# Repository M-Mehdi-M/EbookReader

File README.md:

## MAHMOUDI Mohammadmehdi 332CB 

# Description
EbookReader is an open-source hardware development platform featuring an E-Paper display, environmental sensing, and low-power connectivity options. Perfect for IoT projects, information displays, and environmental monitoring applications.

## 📋 Overview
This project provides a complete hardware platform built around the ESP32-C6 microcontroller with built-in WiFi 6 and Bluetooth 5 LE connectivity. The E-Paper display offers excellent visibility in various lighting conditions with minimal power consumption.

## 🔌 Hardware Architecture and Components

- **Microcontroller**: ESP32-C6-WROOM-1-N8
  - RISC-V core with WiFi 6 and Bluetooth 5 LE
  - Operating at 3.3V

- **Display**: E-Paper display module
  - SPI interface
  - Ultra-low power consumption when not refreshing

- **Storage**: 
  - microSD card slot (SPI)
  - 64MB External NOR Flash (W25Q512JVEIQ)

- **Sensors**:
  - BME688 Environmental sensor (temperature, humidity, pressure, gas)
  - Battery voltage monitoring

- **Power Management**:
  - Li-Po battery charging circuit
  - Fuel gauge (MAX17048G+T10)
  - Low dropout regulator (XC6220A331MR-G)
  - Deep sleep current <10μA

- **Timekeeping**:
  - DS3231SN RTC with temperature compensation

### Expansion Options
- Qwiic/Stemma QT connector for I²C peripherals
- Test pads for debugging

## 🔧 Development Guide

### Getting Started
1. Install the ESP-IDF development framework
2. Clone this repository
3. Connect the board via USB-C
4. Build and flash using ESP-IDF commands

### Example Applications
- Weather station
- Calendar display
- E-ink dashboard
- IoT sensor node
- Low-power data logger

## 📐 Hardware Design Files
The hardware design includes:
- Schematic
- PCB layout
- Bill of Materials
- 3D models of critical components

### Design Notes
- ESD protection on all external interfaces
- Carefully designed power distribution
- Signal integrity considerations for SPI bus
- Separate power domain for E-Paper

## 🔋 Battery Management
- Built-in Li-ion battery charging
- Battery level monitoring
- Low-battery detection and safe shutdown
- Optimized power design for long battery life

## 🛠️ Implementation Steps
1. Review schematic and understand all interfaces
2. Generate PCB layout from schematic
3. Implement power planes and critical routing
4. Add custom design rules for manufacturing
5. Place and route all signals
6. Add 3D models for visualization and mechanical fit

## ✅ Safety Features
- Overcurrent protection
- Reverse polarity protection
- ESD protection on external interfaces
- Thermal management for charging circuit

You can view the "BOM" file [here](Manufacturing/BOM.csv)

You can view the "PICK and PLACE" file [here](Manufacturing/Pick_&_Place.csv)

## 📖 Resources
- [Design & Implementation Guide](https://ocw.cs.pub.ro/courses/tsc/proiect2025)
- [ESP32-C6 Datasheet](https://www.espressif.com/sites/default/files/documentation/esp32-c6_datasheet_en.pdf)

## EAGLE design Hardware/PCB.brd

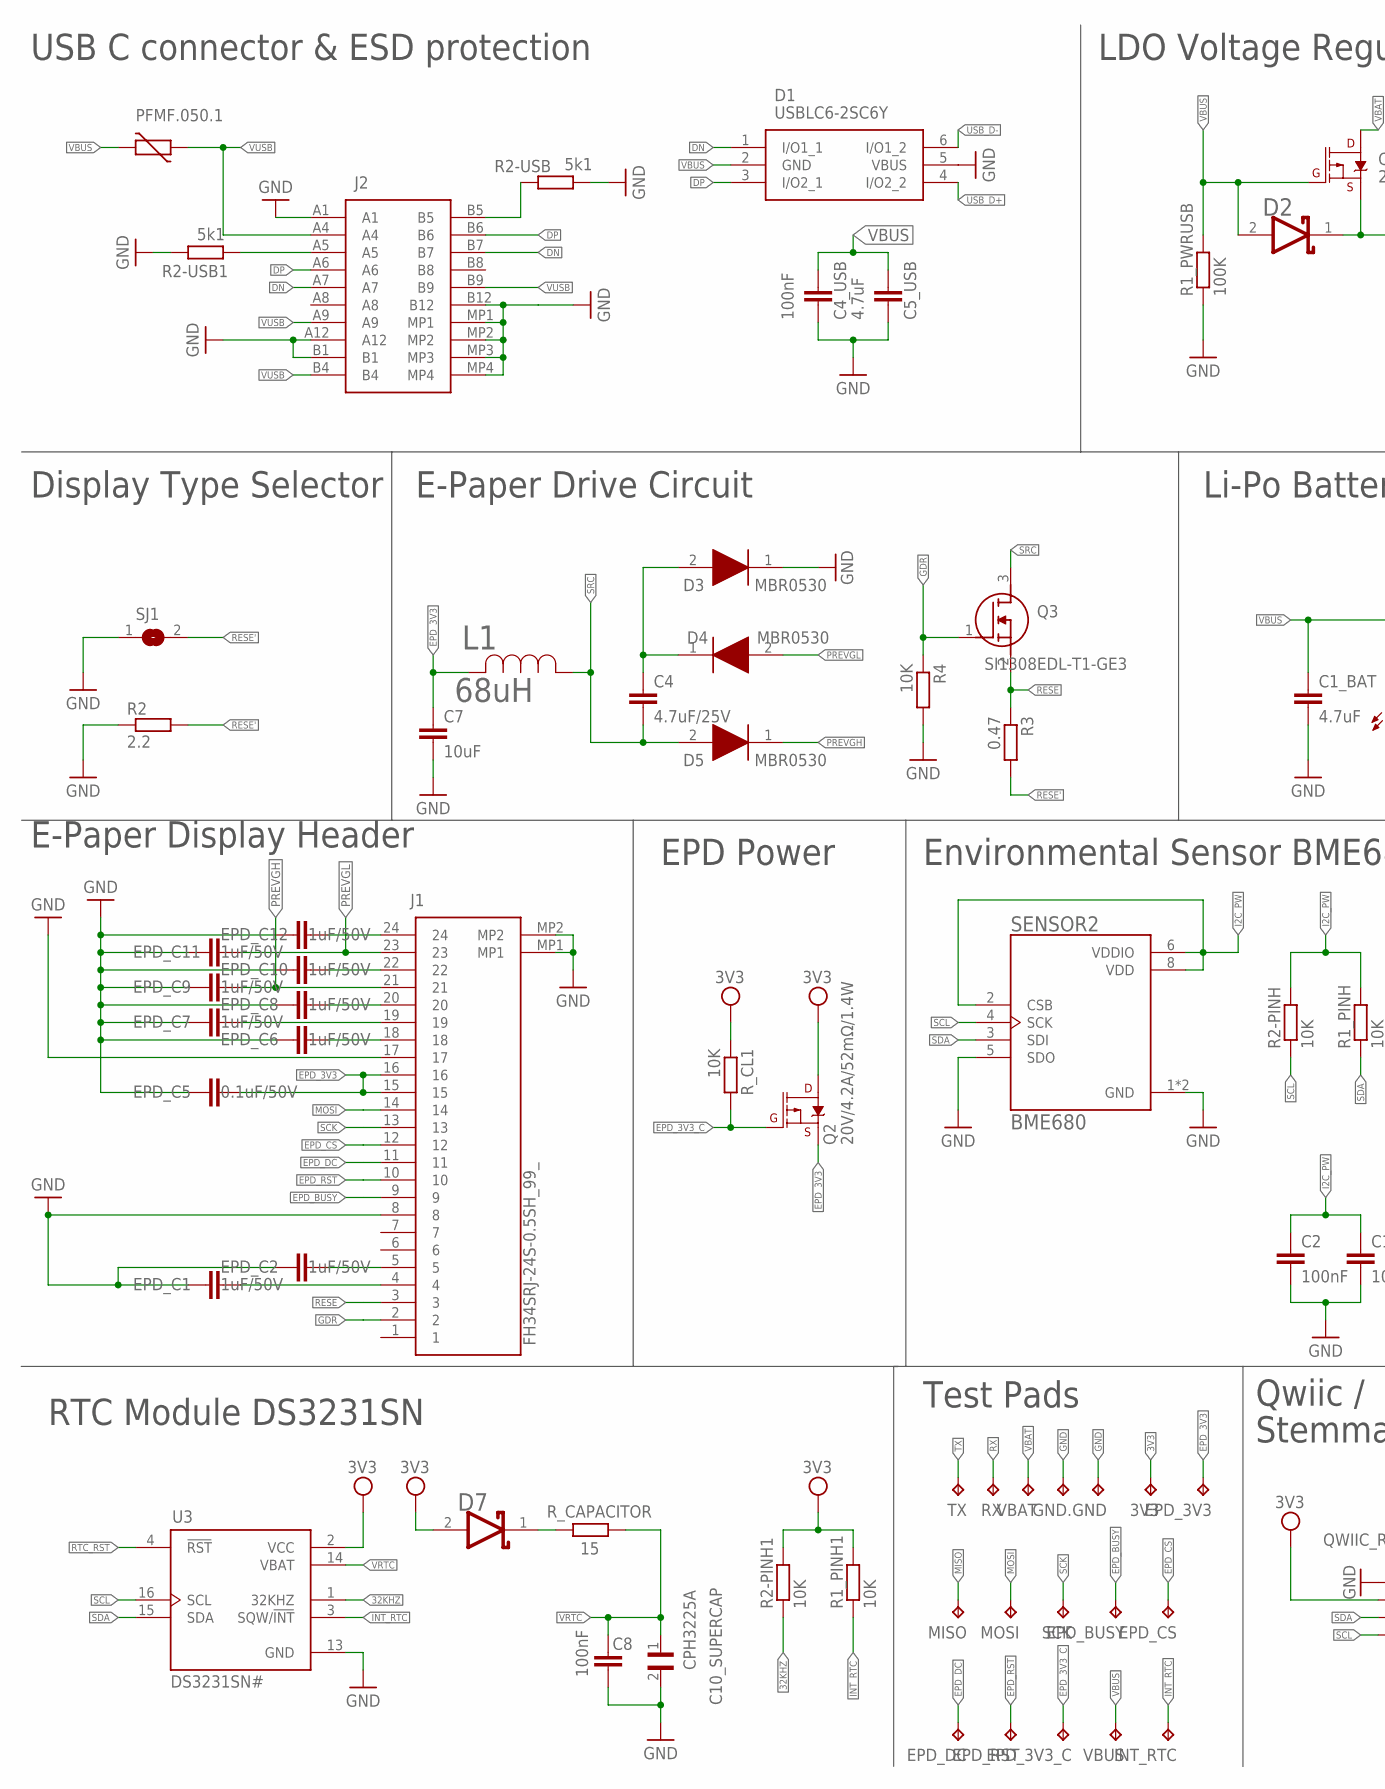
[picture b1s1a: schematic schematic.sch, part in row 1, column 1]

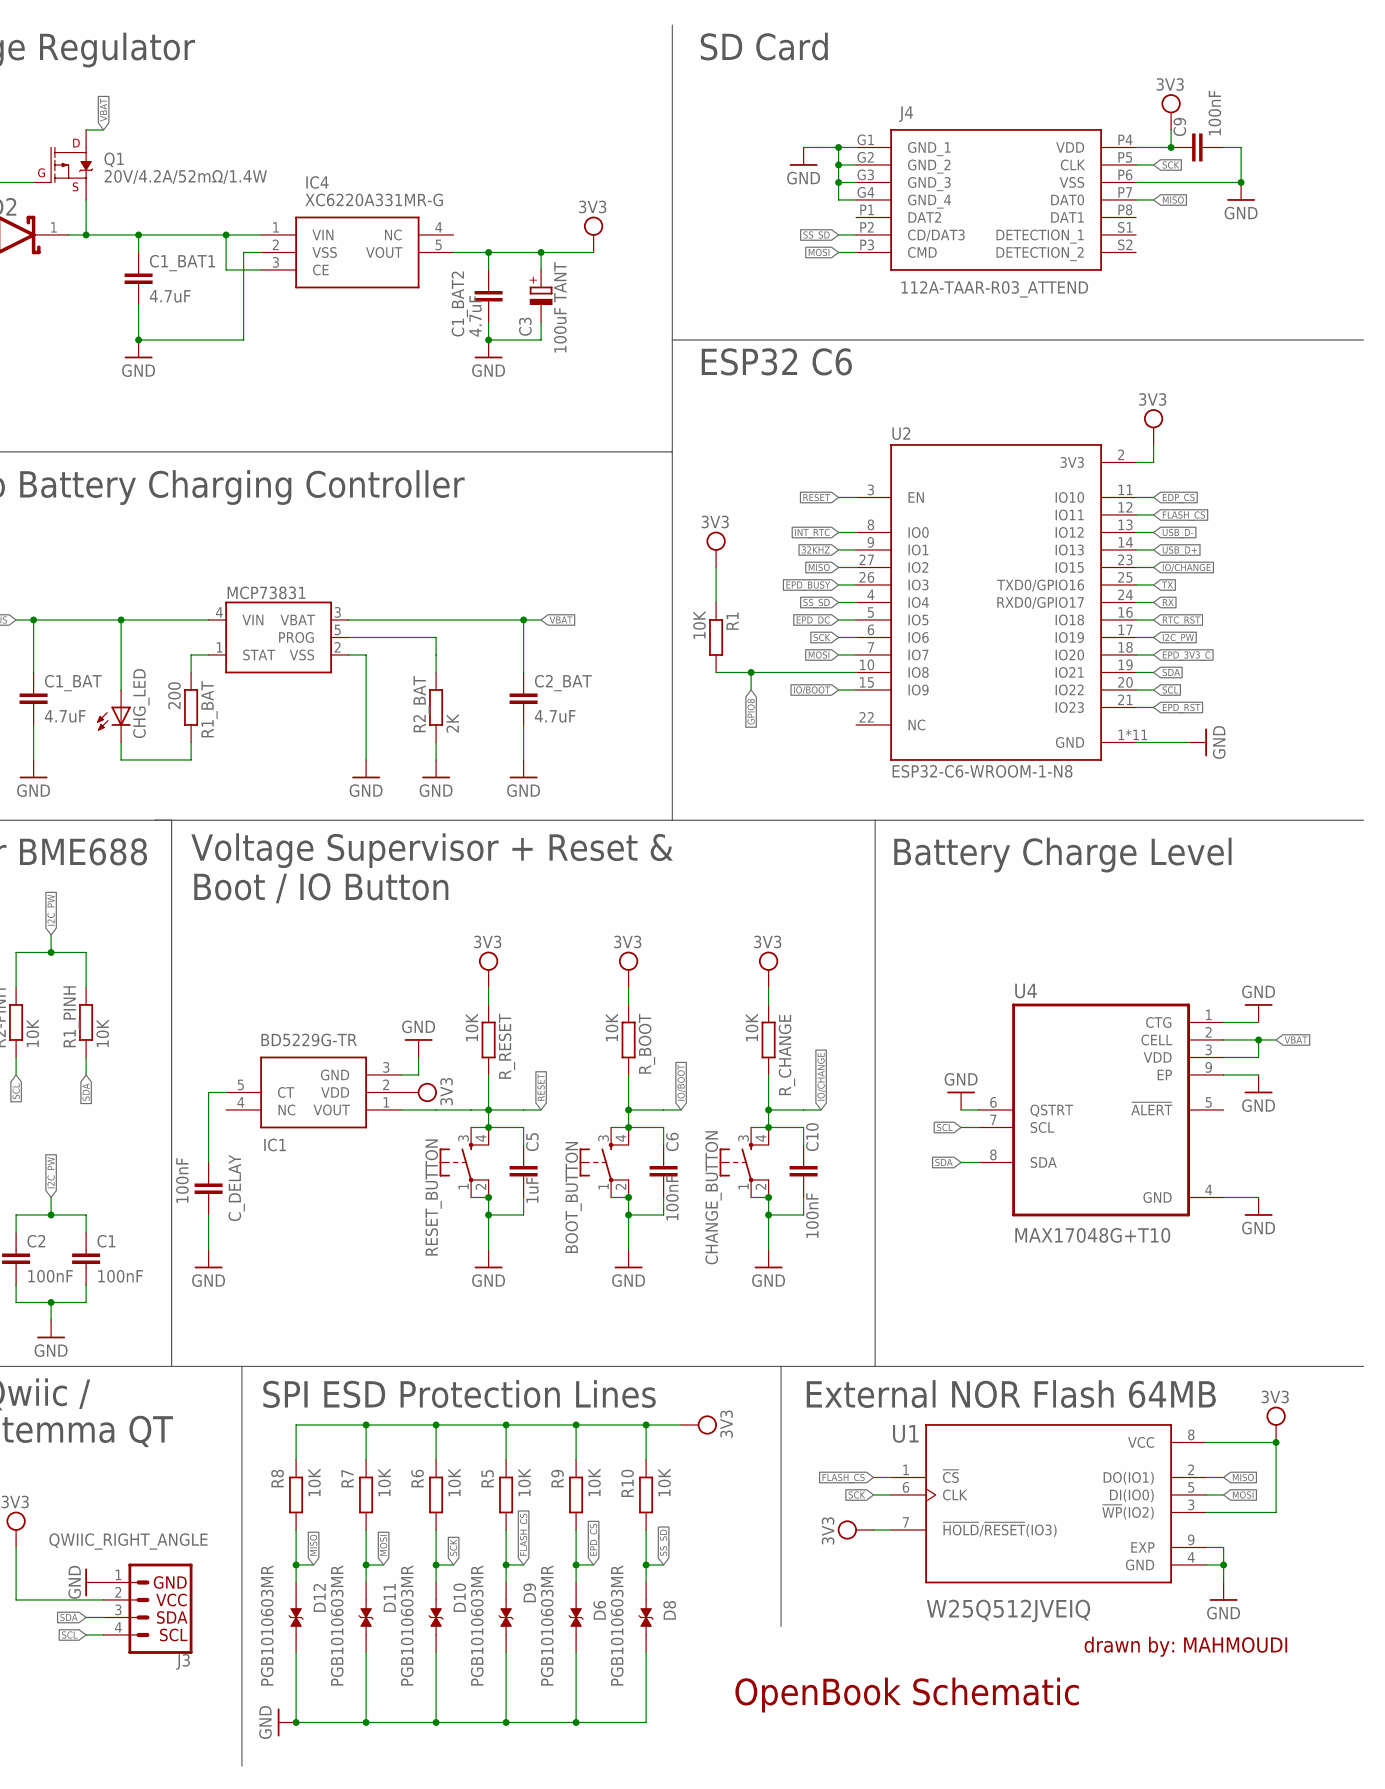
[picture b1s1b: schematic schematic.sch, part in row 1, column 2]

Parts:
3V3: TPTP20R; TP20R
BOOT_BUTTON: BUTTON_CUSYOMV1; MYBUTTON
C1, C2, C6, C8, C9, C10: 100nF; ESP32_WROVER_EAGLE-LTSPICE_C0402
C1_BAT, C2_BAT: 4.7uF; ESP32_WROVER_EAGLE-LTSPICE_C0402
C1_BAT1, C1_BAT2, C5_USB: 4.7uF; EAGLE-LTSPICE_C0402
C3: 100uF TANT; RCL_CT3528
C4: 4.7uF/25V; ESP32_WROVER_EAGLE-LTSPICE_C0402
C4_USB: 100nF; EAGLE-LTSPICE_C0402
C5: 1uF; ESP32_WROVER_EAGLE-LTSPICE_C0402
C7: 10uF; ESP32_WROVER_EAGLE-LTSPICE_C0402
C10_SUPERCAP: CPH3225A; CAPCP3225X100N
CHANGE_BUTTON: BUTTON_CUSYOMV1; MYBUTTON
CHG_LED: ADAFRUIT_LEDCHIP-LED0603; ADAFRUIT_CHIP-LED0603
C_DELAY: 100nF; ESP32_WROVER_EAGLE-LTSPICE_C0402
D1: USBLC6-2SC6Y; SOT95P280X145-6N
D2: ESP32_WROVER_AVX---SD0805S020S1R0_AVX_SD0805S020S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; ESP32_WROVER_AVX---SD0805S020S1R0_AVX_SD0805S020S1R0_0
D3, D4, D5: MBR0530; SOD3716X135N
D6, D8, D9, D10, D11, D12: PGB1010603MR; DIOC1608X36N
D7: SD0805S020S1R0; ESP32_WROVER_AVX---SD0805S020S1R0_AVX_SD0805S020S1R0_0
EPD_3V3, EPD_3V3_C: TPTP20R; TP20R
EPD_BUSY: TPTP20R; TP20R
EPD_C1, EPD_C2, EPD_C6, EPD_C7, EPD_C8, EPD_C9, EPD_C10, EPD_C11, EPD_C12: 1uF/50V; ESP32_WROVER_EAGLE-LTSPICE_C0402
EPD_C5: 0.1uF/50V; ESP32_WROVER_EAGLE-LTSPICE_C0402
EPD_CS: TPTP20R; TP20R
EPD_DC: TPTP20R; TP20R
EPD_RST: TPTP20R; TP20R
GND, GND.: TPTP20R; TP20R
IC1: BD5229G-TR; SOT95P280X125-5N
IC4: XC6220A331MR-G; SOT95P280X120-5N
INT_RTC: TPTP20R; TP20R
J1: FH34SRJ-24S-0.5SH_99_; FH34SRJ24S05SH99
J2: SAMACSYS_PARTS_USB4110-GF-A; SAMACSYS_PARTS_USB4110GFA
J3: QWIIC_RIGHT_ANGLE; JST04_1MM_RA
J4: 112A-TAAR-R03_ATTEND; 112ATAARR03ATTEND
L1: 68uH; IND_4828-WE-TPC_WRE
MCP73831: ESP32_WROVER_SPARKFUN-IC-POWER_MCP73831; ESP32_WROVER_SPARKFUN-IC-POWER_SOT23-5
MISO: TPTP20R; TP20R
MOSI: TPTP20R; TP20R
PFMF.050.1: ESP32C6_VARISTORCN1812; ESP32C6_VARISTOR_CT/CN1812
Q1, Q2: 20V/4.2A/52mΩ/1.4W; ESP32_WROVER_SPARKFUN-DISCRETESEMI_SOT23-3
Q3: SI1308EDL-T1-GE3; SOT65P210X110-3N
R1, R1_PINH, R1_PINH1, R2-PINH, R2-PINH1, R4, R5, R6, R7, R8, R9, R10: 10K; ESP32_WROVER_EAGLE-LTSPICE_R0402
R1_BAT: 200; ESP32_WROVER_EAGLE-LTSPICE_R0402
R1_PWRUSB: 100K; ESP32_WROVER_EAGLE-LTSPICE_R0402
R2: 2.2; ESP32_WROVER_EAGLE-LTSPICE_R0402
R2-USB, R2-USB1: 5k1; ESP32_WROVER_EAGLE-LTSPICE_R0402
R2_BAT: 2K; ESP32_WROVER_EAGLE-LTSPICE_R0402
R3: 0.47; ESP32_WROVER_EAGLE-LTSPICE_R0402
RESET_BUTTON: RESET_BUTTON; MYBUTTON
RX: TPTP20R; TP20R
R_BOOT: 10K; ESP32_WROVER_EAGLE-LTSPICE_R0402
R_CAPACITOR: 15; ESP32_WROVER_EAGLE-LTSPICE_R0402
R_CHANGE: 10K; ESP32_WROVER_EAGLE-LTSPICE_R0402
R_CL1: 10K; ESP32_WROVER_EAGLE-LTSPICE_R0402
R_RESET: 10K; ESP32_WROVER_EAGLE-LTSPICE_R0402
SCK: TPTP20R; TP20R
SENSOR2: BME680; ESP32_WROVER_BME680_PSON80P300X300X100-8N
SJ1: SJ
TX: TPTP20R; TP20R
U1: W25Q512JVEIQ; SON127P600X800X80-9N
U2: ESP32-C6-WROOM-1-N8; XCVR_ESP32-C6-WROOM-1-N8
U3: DS3231SN#; SOIC127P1032X265-16N
U4: MAX17048G+T10; SON50P200X200X80-9N
VBAT: TPTP20R; TP20R
VBUS: TPTP20R; TP20R

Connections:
3V3: 3V3.TP, C1_BAT2.1, C3.+, C9.1, D7.2 (ANODE), IC1.2 (VDD), IC4.5 (VOUT), J3.2, J4.P4 (VDD), Q2.3 (D), R1.1, R1_PINH1.2, R2-PINH1.2, R5.1, R6.1, R7.1, R8.1, R9.1, R10.1, R_BOOT.1, R_CHANGE.1, R_CL1.1, R_RESET.1, U1.3 (!WP!(IO2)), U1.7 (!HOLD!/!RESET!(IO3)), U1.8 (VCC), U2.2 (3V3), U3.2 (VCC)
32KHZ: R2-PINH1.1, U2.9 (IO1), U3.1 (32KHZ)
DN: D1.1 (I/O1_1), J2.A7, J2.B7
DP: D1.3 (I/O2_1), J2.A6, J2.B6
EDP_CS: U2.11 (IO10)
EPD_3V3: C7.1, EPD_3V3.TP, EPD_C5.2, J1.15, J1.16, L1.2, Q2.2 (S)
EPD_3V3_C: EPD_3V3_C.TP, Q2.1 (G), R_CL1.2, U2.18 (IO20)
EPD_BUSY: EPD_BUSY.TP, J1.9, U2.26 (IO3)
EPD_CS: D6.1, EPD_CS.TP, J1.12, R9.2
EPD_DC: EPD_DC.TP, J1.11, U2.5 (IO5)
EPD_RST: EPD_RST.TP, J1.10, U2.21 (IO23)
FLASH_CS: D9.1, R5.2, U1.1 (!CS), U2.12 (IO11)
GDR: J1.2, Q3.1 (G), R4.1
GND: BOOT_BUTTON.1, BOOT_BUTTON.2, C1.2, C1_BAT.2, C1_BAT1.2, C1_BAT2.2, C2.2, C2_BAT.2, C3.-, C4_USB.2, C5.2, C5_USB.2, C6.2, C7.2, C8.2, C9.2, C10.2, C10_SUPERCAP.2, CHANGE_BUTTON.1, CHANGE_BUTTON.2, C_DELAY.2, D1.5 (VBUS), D3.1 (K), D6.2, D8.2, D9.2, D10.2, D11.2, D12.2, EPD_C1.1, EPD_C2.1, EPD_C5.1, EPD_C6.1, EPD_C7.1, EPD_C8.1, EPD_C9.1, EPD_C10.1, EPD_C11.1, EPD_C12.1, GND.TP, GND..TP, IC1.3 (GND), IC4.2 (VSS), J1.8, J1.17, J1.MP1, J1.MP2, J2.A1, J2.A12, J2.B1, J2.B12, J2.MP1, J2.MP2, J2.MP3, J2.MP4, J3.1, J4.G1 (GND_1), J4.G2 (GND_2), J4.G3 (GND_3), J4.G4 (GND_4), J4.P6 (VSS), MCP73831.2 (VSS), R1_PWRUSB.1, R2.1, R2-USB.2, R2-USB1.1, R2_BAT.1, R4.2, RESET_BUTTON.1, RESET_BUTTON.2, SENSOR2.1 (GND), SENSOR2.5 (SDO), SENSOR2.7 (GND), SJ1.1, U1.4 (GND), U1.9 (EXP), U2.1 (GND), U2.28 (GND), U2.29_1 (GND), U2.29_2 (GND), U2.29_3 (GND), U2.29_4 (GND), U2.29_5 (GND), U2.29_6 (GND), U2.29_7 (GND), U2.29_8 (GND), U2.29_9 (GND), U3.13 (GND), U4.1 (CTG), U4.4 (GND), U4.6 (QSTRT), U4.9 (EP)
GPIO8: R1.2, U2.10 (IO8)
I2C_PW: C1.1, C2.1, R1_PINH.2, R2-PINH.2, SENSOR2.2 (CSB), SENSOR2.6 (VDDIO), SENSOR2.8 (VDD), U2.17 (IO19)
INT_RTC: INT_RTC.TP, R1_PINH1.1, U2.8 (IO0), U3.3 (SQW/!INT)
IO/BOOT: BOOT_BUTTON.3, BOOT_BUTTON.4, C6.1, R_BOOT.2, U2.15 (IO9)
IO/CHANGE: C10.1, CHANGE_BUTTON.3, CHANGE_BUTTON.4, R_CHANGE.2, U2.23 (IO15)
MISO: D12.1, J4.P7 (DAT0), MISO.TP, R8.2, U1.2 (DO(IO1)), U2.27 (IO2)
MOSI: D11.1, J1.14, J4.P3 (CMD), MOSI.TP, R7.2, U1.5 (DI(IO0)), U2.7 (IO7)
unnamed: J2.B5, R2-USB.1
unnamed: J2.A5, R2-USB1.2
unnamed: EPD_C2.2, J1.5
unnamed: C1_BAT1.1, D2.1 (CATHODE), IC4.1 (VIN), IC4.3 (CE), Q1.2 (S)
unnamed: MCP73831.5 (PROG), R2_BAT.2
unnamed: MCP73831.1 (STAT), R1_BAT.1
unnamed: CHG_LED.C, R1_BAT.2
unnamed: C4.1, D3.2 (A), D4.1 (K)
unnamed: EPD_C1.2, J1.4
unnamed: EPD_C12.2, J1.24
unnamed: EPD_C10.2, J1.22
unnamed: EPD_C8.2, J1.20
unnamed: EPD_C7.2, J1.19
unnamed: EPD_C6.2, J1.18
unnamed: C_DELAY.1, IC1.5 (CT)
unnamed: D7.1 (CATHODE), R_CAPACITOR.2
PREVGH: D5.1 (K), EPD_C9.2, J1.21
PREVGL: D4.2 (A), EPD_C11.2, J1.23
RESE: J1.3, Q3.2 (S), R3.1
RESE': R2.2, R3.2, SJ1.2
RESET: C5.1, IC1.1 (VOUT), RESET_BUTTON.3, RESET_BUTTON.4, R_RESET.2, U2.3 (EN)
RTC_RST: U2.16 (IO18), U3.4 (!RST)
RX: RX.TP, U2.24 (RXD0/GPIO17)
SCK: D10.1, J1.13, J4.P5 (CLK), R6.2, SCK.TP, U1.6 (CLK), U2.6 (IO6)
SCL: J3.4, R2-PINH.1, SENSOR2.4 (SCK), U2.20 (IO22), U3.16 (SCL), U4.7 (SCL)
SDA: J3.3, R1_PINH.1, SENSOR2.3 (SDI), U2.19 (IO21), U3.15 (SDA), U4.8 (SDA)
SRC: C4.2, D5.2 (A), L1.1, Q3.3 (D)
SS_SD: D8.1, J4.P2 (CD/DAT3), R10.2, U2.4 (IO4)
TX: TX.TP, U2.25 (TXD0/GPIO16)
USB_D+: D1.4 (I/O2_2), U2.14 (IO13)
USB_D-: D1.6 (I/O1_2), U2.13 (IO12)
VBAT: C2_BAT.1, MCP73831.3 (VBAT), Q1.3 (D), U4.2 (CELL), U4.3 (VDD), VBAT.TP
VBUS: C1_BAT.1, C4_USB.1, C5_USB.1, CHG_LED.A, D1.2 (GND), D2.2 (ANODE), MCP73831.4 (VIN), PFMF.050.1.2, Q1.1 (G), R1_PWRUSB.2, VBUS.TP
VRTC: C8.1, C10_SUPERCAP.1, R_CAPACITOR.1, U3.14 (VBAT)
VUSB: J2.A4, J2.A9, J2.B4, J2.B9, PFMF.050.1.1

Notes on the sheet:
drawn by: MAHMOUDI
SD Card
ESP32 C6
USB C connector & ESD protection
LDO Voltage Regulator
Li-Po Battery Charging Controller
E-Paper Drive Circuit
Display Type Selector
RTC Module DS3231SN
Test Pads
Qwiic / Stemma QT
SPI ESD Protection Lines
External NOR Flash 64MB
OpenBook Schematic
E-Paper Display Header
EPD Power
Environmental Sensor BME688
Voltage Supervisor + Reset & Boot / IO Button
Battery Charge Level

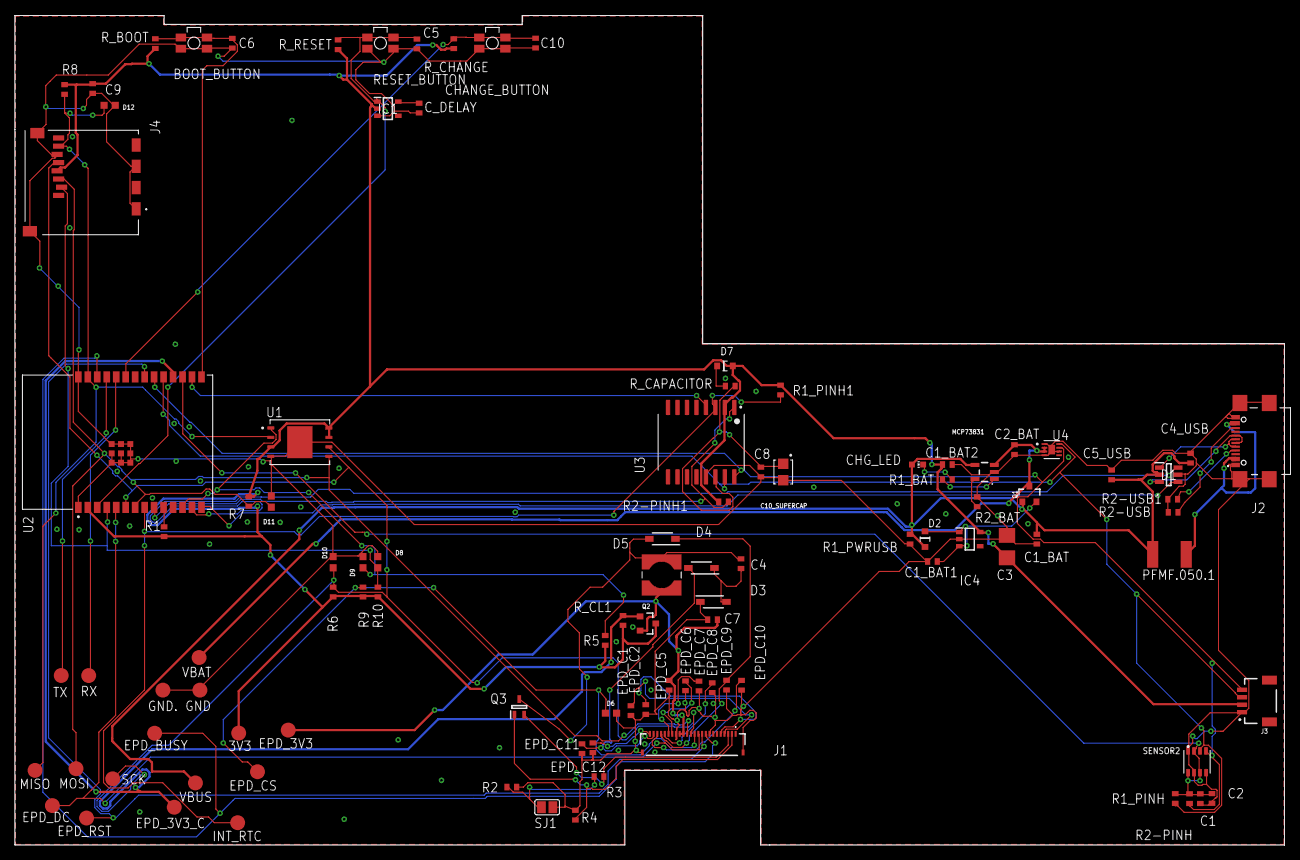
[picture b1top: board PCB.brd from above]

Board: 2 copper layers, 170.2 x 111.2 mm, 103 parts (0 on the bottom side), 55 nets.

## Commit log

2025-04-05 Create LICENSE
2025-04-05 add files
2025-04-06 add files"
2025-04-06 Update LICENSE

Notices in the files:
README.md:
License: MIT
parts and their libraries:
COPYRIGHT: Copyright (C) 2024 Ultra Librarian. All rights reserved.
